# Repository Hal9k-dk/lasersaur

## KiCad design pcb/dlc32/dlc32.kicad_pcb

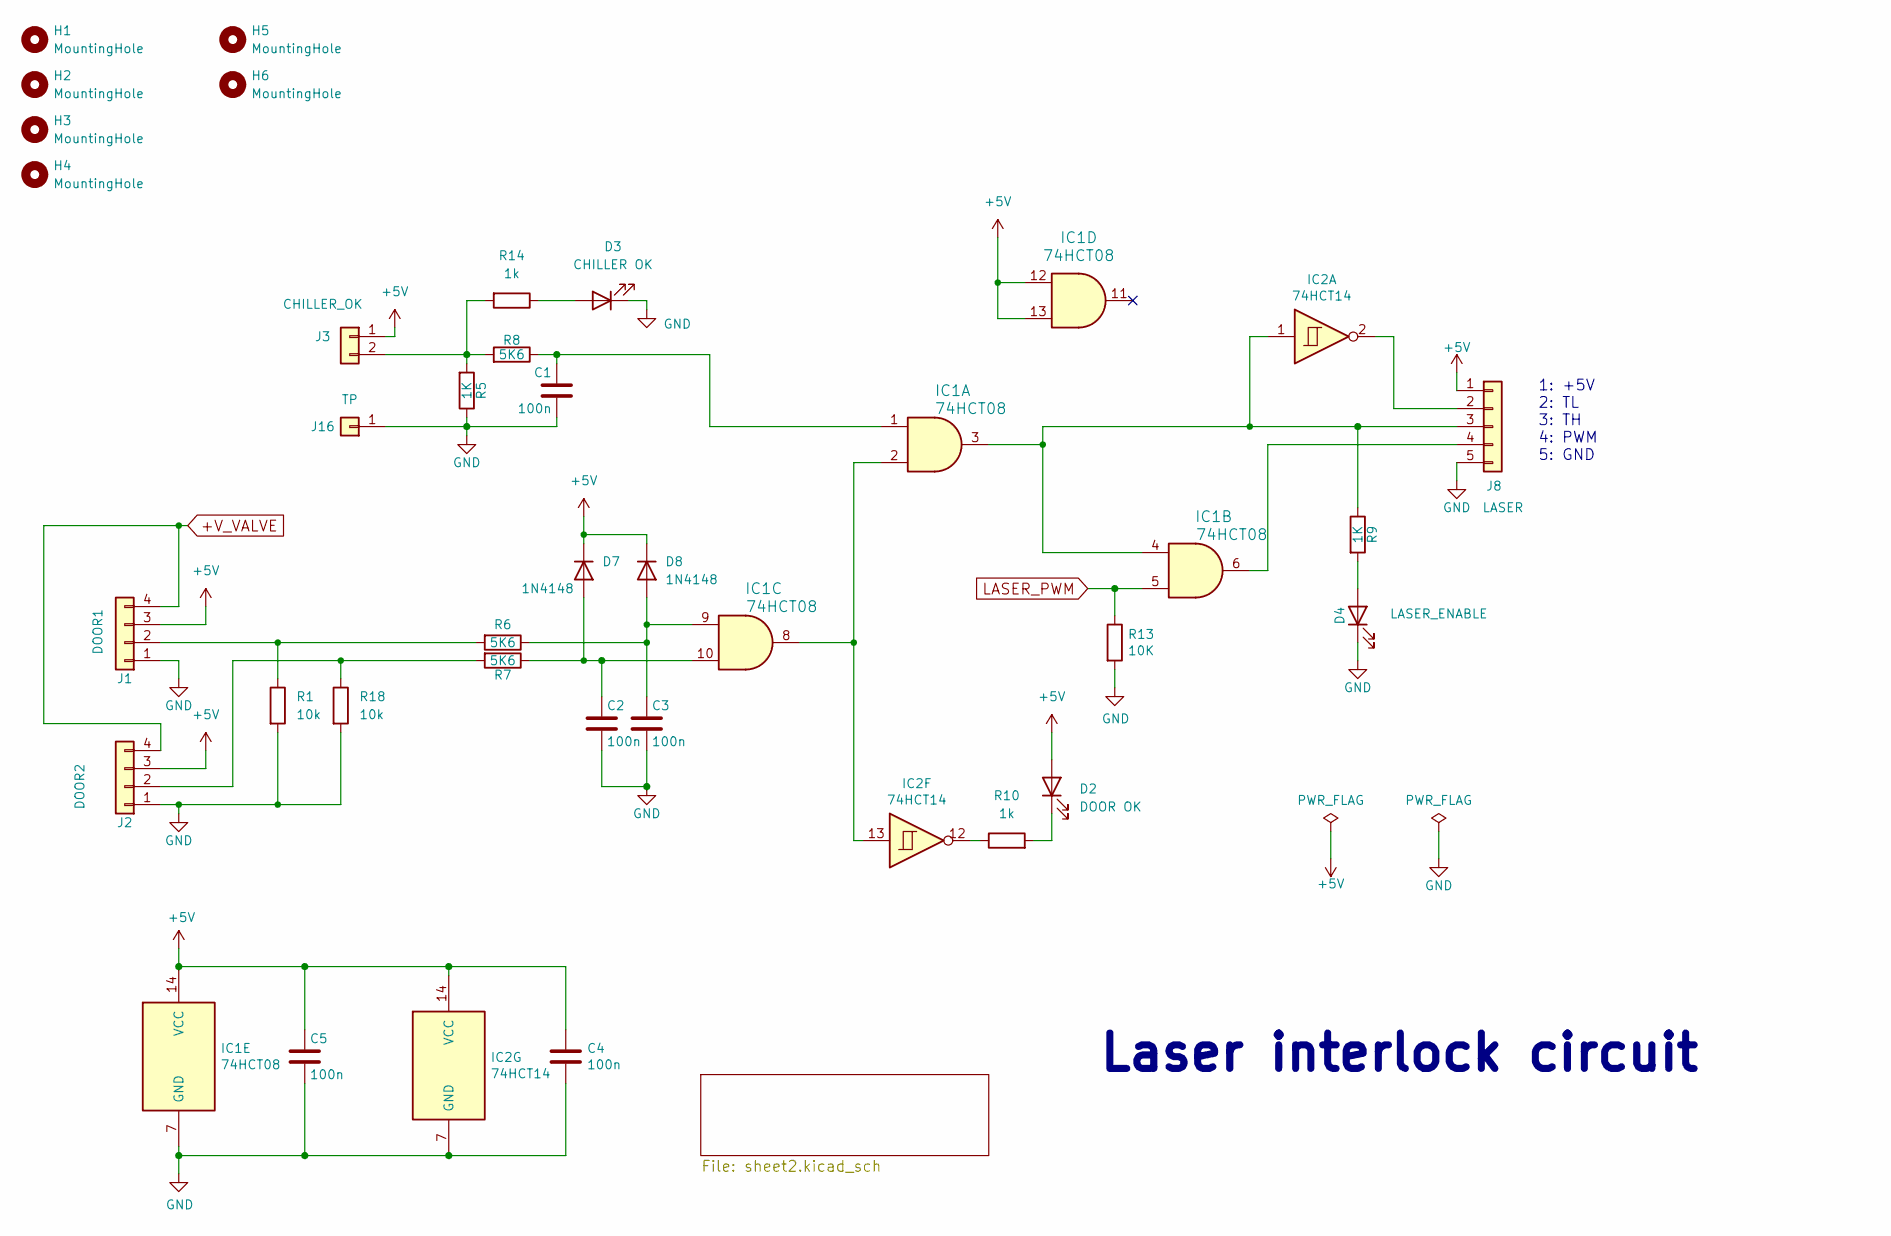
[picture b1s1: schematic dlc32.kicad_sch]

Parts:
C1, C2, C3, C4, C5: 100n; C_0603_1608Metric
D2: DOOR OK; LED_D5.0mm_Horizontal_O1.27mm_Z3.0mm
D3: CHILLER OK; LED_D5.0mm_Horizontal_O1.27mm_Z3.0mm
D4: LASER_ENABLE; LED_D5.0mm_Horizontal_O1.27mm_Z3.0mm
D7, D8: 1N4148; D_MiniMELF
H1, H2, H3, H4, H5, H6: MountingHole; MountingHole_3.2mm_M3
IC1: 74HCT08; SOIC-14_3.9x8.7mm_P1.27mm
IC2: 74HCT14; SOIC-14_3.9x8.7mm_P1.27mm
J1: DOOR1; JST_XH_B4B-XH-A_1x04_P2.50mm_Vertical
J2: DOOR2; JST_XH_B4B-XH-A_1x04_P2.50mm_Vertical
J3: CHILLER_OK; JST_XH_B2B-XH-A_1x02_P2.50mm_Vertical
J8: LASER; JST_XH_B5B-XH-A_1x05_P2.50mm_Vertical
J16: TP; TestPoint_Loop_D1.80mm_Drill1.0mm_Beaded
R1, R18: 10k; R_0603_1608Metric
R5, R9: 1K; R_0603_1608Metric
R6, R7, R8: 5K6; R_0603_1608Metric
R10, R14: 1k; R_0603_1608Metric
R13: 10K; R_0603_1608Metric

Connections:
+5V: C4.1, C5.1, D2.2 (A), D7.1 (K), D8.1 (K), IC1.12, IC1.13, IC1.14 (VCC), IC2.14 (VCC), J1.3, J2.3, J3.1, J8.1; also elsewhere on the board
+V_VALVE: J1.4, J2.4; also elsewhere on the board
GND: C1.2, C2.2, C3.2, C4.2, C5.2, D3.1 (K), D4.1 (K), IC1.7 (GND), IC2.7 (GND), J1.1, J2.1, J8.5, J16.1, R1.2, R5.1, R13.2, R18.2; also elsewhere on the board
LASER_PWM: IC1.5, R13.1; also elsewhere on the board
unnamed: C1.1, IC1.1, R8.1
unnamed: D2.1 (K), R10.2
unnamed: D3.2 (A), R14.1
unnamed: D4.2 (A), R9.2
unnamed: C2.1, D7.2 (A), IC1.10, R7.1
unnamed: C3.1, D8.2 (A), IC1.9, R6.1
unnamed: IC1.2, IC1.8, IC2.13
unnamed: IC2.12, R10.1
unnamed: J1.2, R1.1, R6.2
unnamed: J2.2, R7.2, R18.1
unnamed: J3.2, R5.2, R8.2, R14.2
unnamed: IC2.2, J8.2
unnamed: IC1.3, IC1.4, IC2.1, J8.3, R9.1
unnamed: IC1.6, J8.4

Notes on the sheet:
Laser interlock circuit
1: +5V 2: TL 3: TH 4: PWM 5: GND

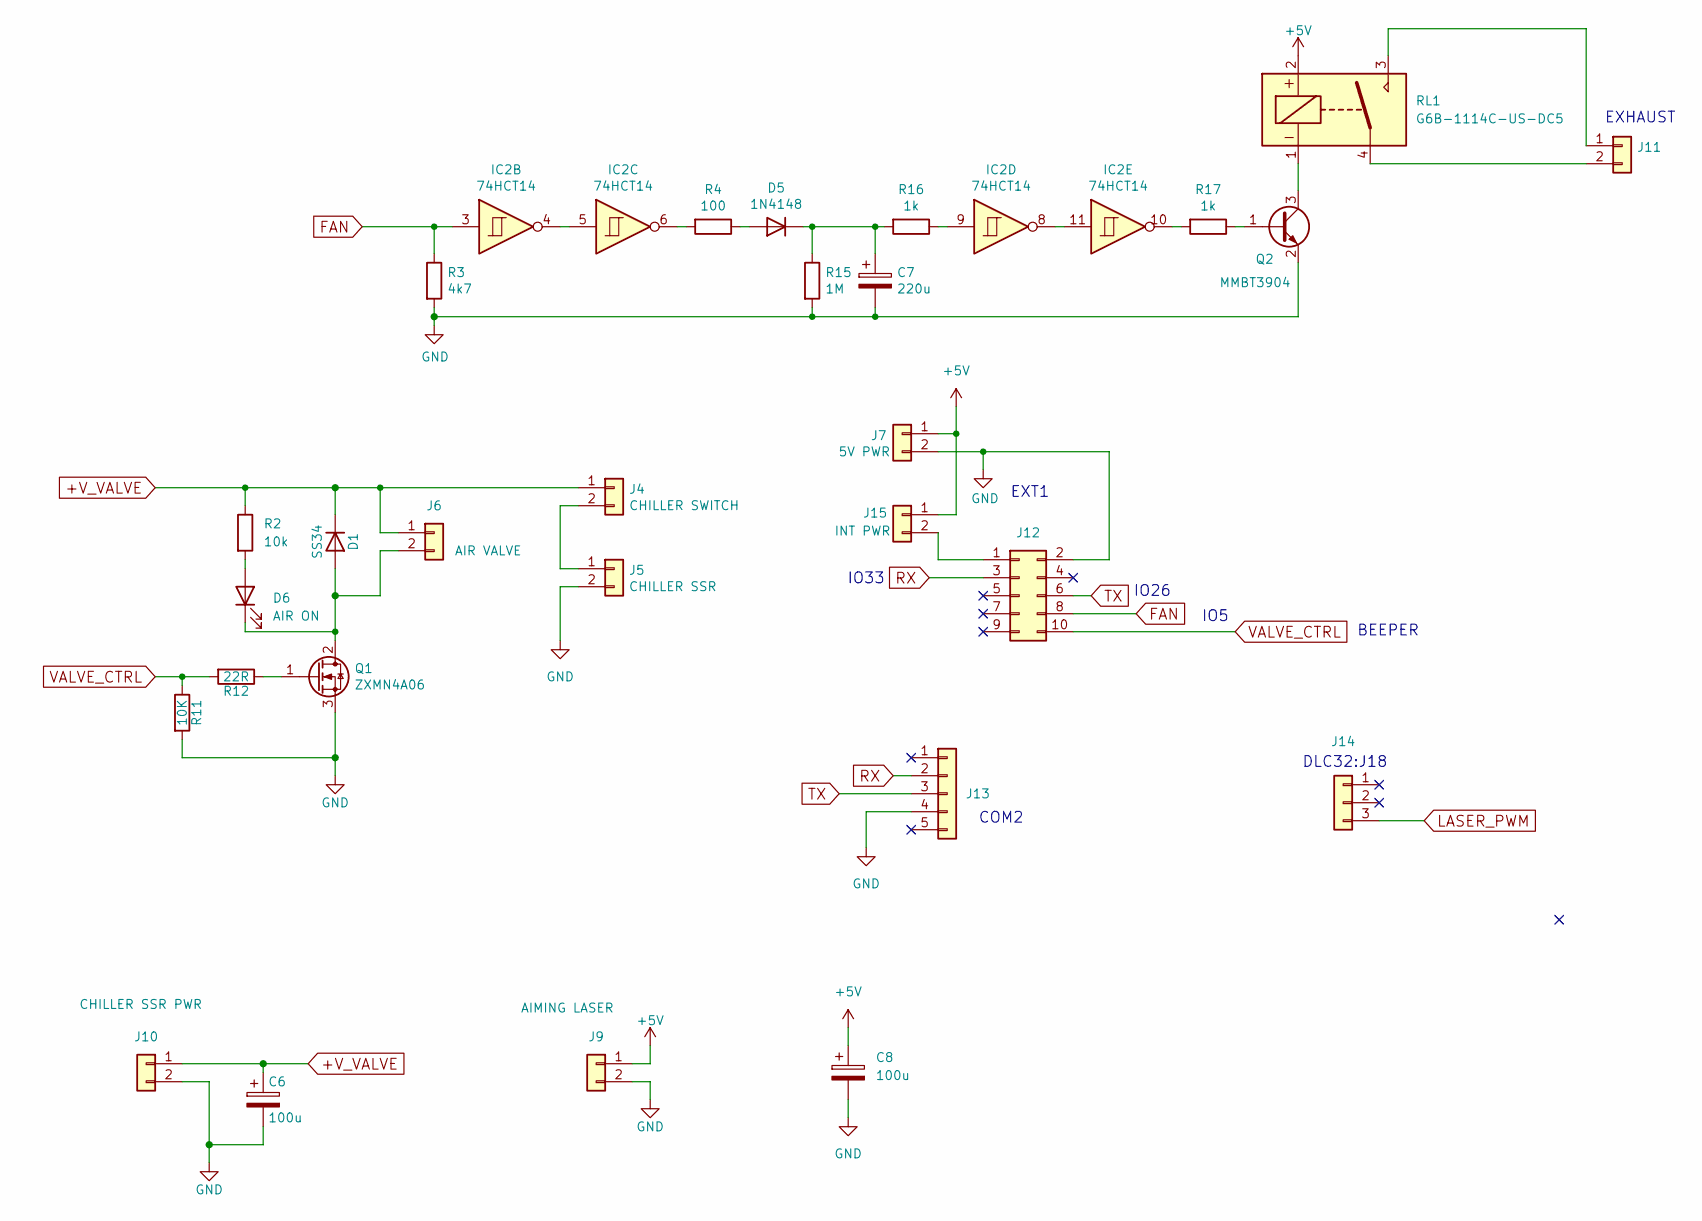
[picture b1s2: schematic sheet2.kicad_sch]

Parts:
C6, C8: 100u; CP_Elec_10x10
C7: 220u; CP_EIA-7343-15_Kemet-W
D1: SS34; D_SMA
D5: 1N4148; D_MiniMELF
D6: AIR ON; LED_D5.0mm_Horizontal_O1.27mm_Z3.0mm
IC2: 74HCT14; SOIC-14_3.9x8.7mm_P1.27mm
J4: CHILLER SWITCH; JST_XH_B2B-XH-A_1x02_P2.50mm_Vertical
J5: CHILLER SSR; JST_XH_B2B-XH-A_1x02_P2.50mm_Vertical
J6: AIR VALVE; JST_XH_B2B-XH-A_1x02_P2.50mm_Vertical
J7: 5V PWR; JST_XH_B2B-XH-A_1x02_P2.50mm_Vertical
J9: AIMING LASER; JST_XH_B2B-XH-A_1x02_P2.50mm_Vertical
J10: CHILLER SSR PWR; JST_XH_B2B-XH-A_1x02_P2.50mm_Vertical
J11: EXHAUST; JST_XH_B2B-XH-A_1x02_P2.50mm_Vertical
J12: EXT1; IDC-Header_2x05_P2.54mm_Vertical
J13: COM2; PinHeader_1x05_P2.54mm_Vertical
J14: DLC32:J18; JST_XH_B3B-XH-A_1x03_P2.50mm_Vertical
J15: INT PWR; PinHeader_1x02_P2.54mm_Vertical
Q1: ZXMN4A06; SOT-223-3_TabPin2
Q2: MMBT3904; SOT-23
R2: 10k; R_0603_1608Metric
R3: 4k7; R_0603_1608Metric
R4: 100; R_0603_1608Metric
R11: 10K; R_0603_1608Metric
R12: 22R; R_0603_1608Metric
R15: 1M; R_0603_1608Metric
R16, R17: 1k; R_0603_1608Metric
RL1: G6B-1114C-US-DC5; DIL-relay

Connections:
+5V: C8.1, J7.1, J9.1, J15.1, RL1.2; also elsewhere on the board
+V_VALVE: C6.1, D1.1 (K), J4.1, J6.1, J10.1, R2.1; also elsewhere on the board
FAN: IC2.3, J12.8, R3.1
GND: C6.2, C7.2, C8.2, J5.2, J7.2, J9.2, J10.2, J12.2, J13.4, Q1.3 (S), Q2.2 (E), R3.2, R11.2, R15.2; also elsewhere on the board
LASER_PWM: J14.3; also elsewhere on the board
unnamed: D1.2 (A), D6.1 (K), J6.2, Q1.2 (D)
unnamed: D5.2 (A), R4.1
unnamed: C7.1, D5.1 (K), R15.1, R16.2
unnamed: D6.2 (A), R2.2
unnamed: IC2.4, IC2.5
unnamed: IC2.6, R4.2
unnamed: IC2.9, R16.1
unnamed: IC2.10, R17.2
unnamed: IC2.8, IC2.11
unnamed: J4.2, J5.1
unnamed: J11.1, RL1.3
unnamed: J11.2, RL1.4
unnamed: J12.1, J15.2
unnamed: Q1.1 (G), R12.1
unnamed: Q2.1 (B), R17.1
unnamed: Q2.3 (C), RL1.1
RX: J12.3, J13.2
TX: J12.6, J13.3
VALVE_CTRL: J12.10, R11.1, R12.2

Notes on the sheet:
EXT1
EXHAUST
DLC32:J18
COM2
IO33
IO5
BEEPER
IO26

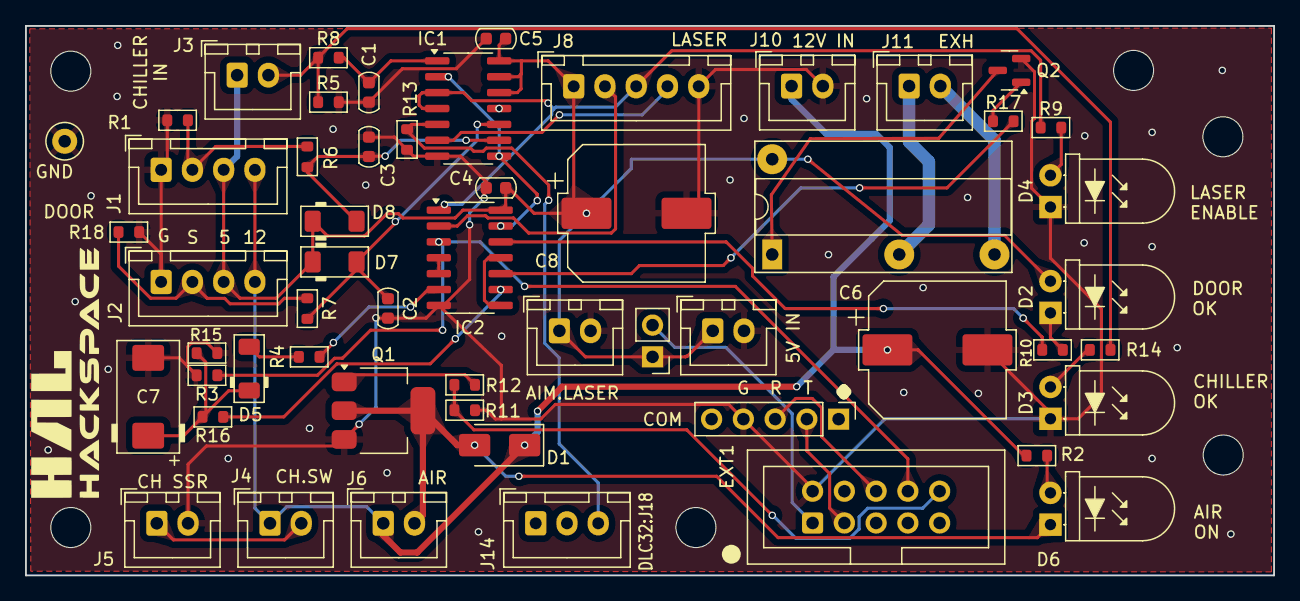
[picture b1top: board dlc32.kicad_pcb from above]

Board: 2 copper layers, 99.8 x 43.9 mm, 61 parts (0 on the bottom side), 38 nets.

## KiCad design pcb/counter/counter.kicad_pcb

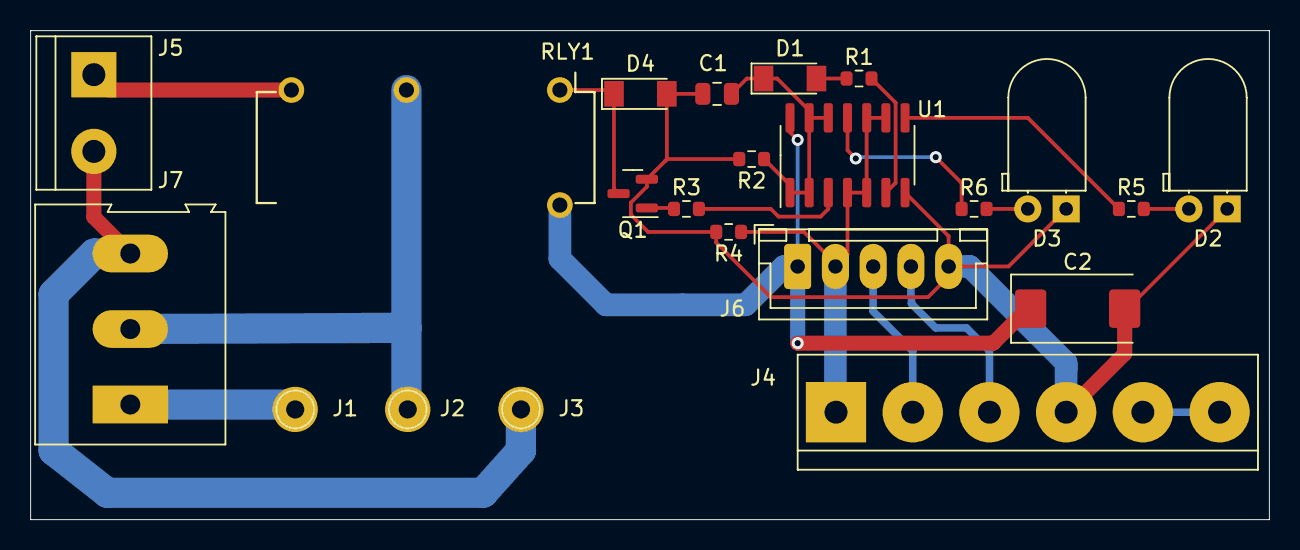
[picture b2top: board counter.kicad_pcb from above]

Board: 2 copper layers, 82.0 x 32.4 mm, 22 parts (0 on the bottom side), 20 nets.

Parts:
C1: 10u; C_0805_2012Metric
C2: 100u; CP_EIA-7343-40_Kemet-Y
D1, D4: 1N4148; D_MiniMELF
D2, D3: LED; LED_D5.0mm_Horizontal_O1.27mm_Z3.0mm
J1, J2, J3: Conn_01x01; Pin_D1.0mm_L10.0mm
J4: 0.2"; TerminalBlock_bornier-6_P5.08mm
J5: 0.2"; TerminalBlock_bornier-2_P5.08mm
J6: JST XH; JST_XH_B05B-XH-A_1x05_P2.50mm_Vertical
J7: 0.2"; TerminalBlock_Altech_AK300-3_P5.00mm
Q1: MMBT3904; SOT-23
R1: 100; R_0603_1608Metric
R2: 1M; R_0603_1608Metric
R3: 1k; R_0603_1608Metric
R4: 100k; R_0603_1608Metric
R5, R6: 820; R_0603_1608Metric
RLY1: RELAY_DIL16; DIP-16_Relay
U1: 74HCT08; SOIC-14_3.9x8.7mm_P1.27mm

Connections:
+5V: C2.1, J6.1, RLY1.16, U1.14 (VCC)
GND: C1.2, C2.2, D2.1 (K), D3.1 (K), D4.2 (A), J4.4, J6.5, Q1.2 (E), R2.2, R4.2, U1.7 (GND)
unnamed: C1.1, D1.1 (K), R2.1, U1.1, U1.2, U1.12, U1.13
unnamed: D1.2 (A), R1.1
unnamed: D2.2 (A), R5.2
unnamed: D3.2 (A), R6.2
unnamed: J1.1, J7.1
unnamed: J2.1, J7.2, RLY1.5
unnamed: J3.1, J5.2, J7.3
unnamed: J4.2, J6.3
unnamed: J4.3, J6.4
unnamed: J4.5, J4.6
unnamed: J5.1, RLY1.8
unnamed: Q1.1 (B), R3.1
unnamed: R1.2, U1.6
unnamed: R3.2, U1.3
unnamed: R5.1, U1.8
unnamed: R6.1, U1.11
RELAY: D4.1 (K), Q1.3 (C), RLY1.1
TH: J4.1, J6.2, R4.1, U1.4, U1.5, U1.9, U1.10

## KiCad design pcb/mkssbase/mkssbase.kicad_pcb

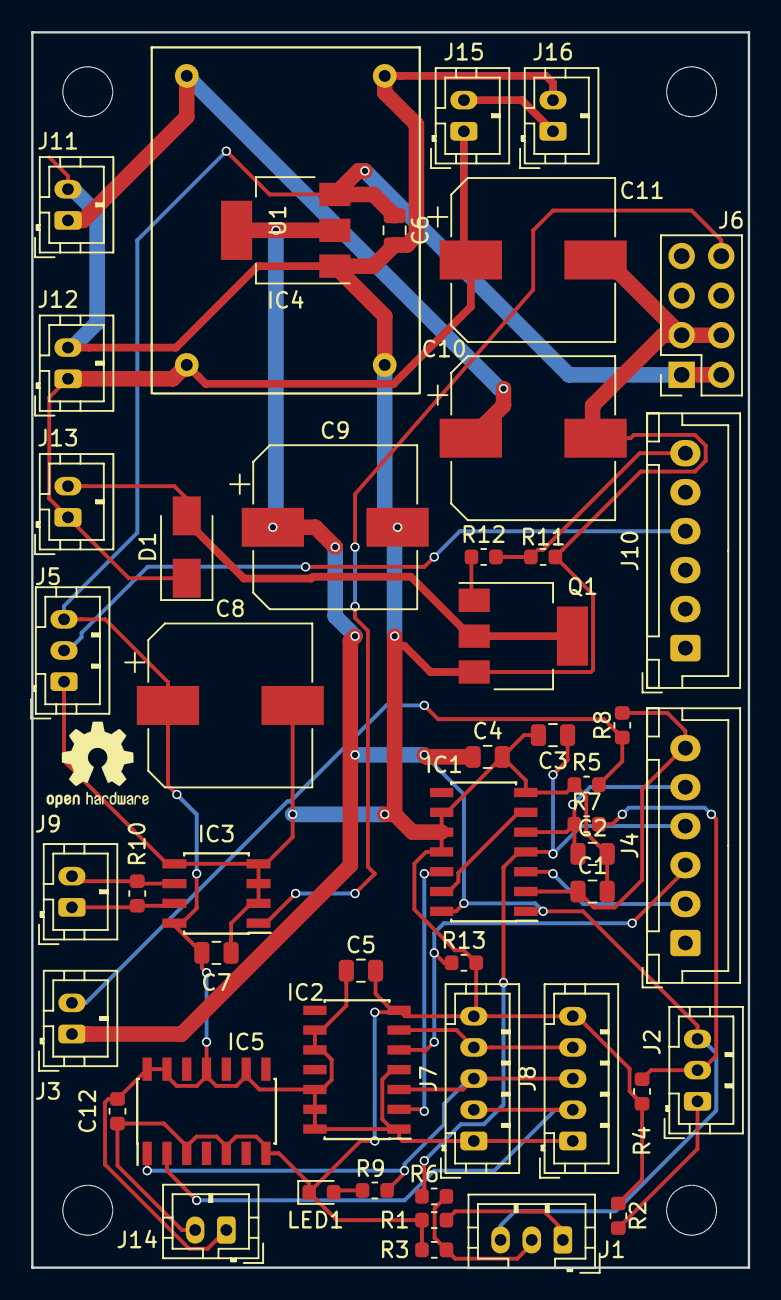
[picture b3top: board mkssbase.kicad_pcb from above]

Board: 2 copper layers, 46.0 x 79.2 mm, 50 parts (0 on the bottom side), 29 nets.

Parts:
C1, C2, C3, C4, C5, C6, C7: 100n; C_0805_2012Metric
C8, C9, C10, C11: 100u; CP_Elec_10x10
C12: 100n; C_0603_1608Metric
D1: SS34; D_SMA
IC1: 74LV11; SOIC-14_3.9x8.7mm_P1.27mm
IC2: 74HCT08; SOIC-14_3.9x8.7mm_P1.27mm
IC3: MAX485E; SOIC-8_3.9x4.9mm_P1.27mm
IC4: AMS1117-3.3; SOT-223-3_TabPin2
IC5: 74HCT04; SOIC-14_3.9x8.7mm_P1.27mm
J1: DOOR1; JST_PH_B3B-PH-K_1x03_P2.00mm_Vertical
J2: DOOR2; JST_PH_B3B-PH-K_1x03_P2.00mm_Vertical
J3: CHILLER; JST_PH_B2B-PH-K_1x02_P2.00mm_Vertical
J4: TO_J8; JST_XH_B06B-XH-A_1x06_P2.50mm_Vertical
J5: POWEROFF; JST_PH_B3B-PH-K_1x03_P2.00mm_Vertical
J6: Conn_02x04_Odd_Even; PinSocket_2x04_P2.54mm_Vertical
J7: LASER_AUX; JST_PH_B5B-PH-K_1x05_P2.00mm_Vertical
J8: LASER; JST_PH_B5B-PH-K_1x05_P2.00mm_Vertical
J9: CHILLER SERIAL; JST_PH_B2B-PH-K_1x02_P2.00mm_Vertical
J10: TO_J7; JST_XH_B06B-XH-A_1x06_P2.50mm_Vertical
J11: 24V PWR; JST_PH_B2B-PH-K_1x02_P2.00mm_Vertical
J12: LED LIGHTING; JST_PH_B2B-PH-K_1x02_P2.00mm_Vertical
J13: AIR VALVE; JST_PH_B2B-PH-K_1x02_P2.00mm_Vertical
J14: AIMING LASER; JST_PH_B2B-PH-K_1x02_P2.00mm_Vertical
J15: CHILLER POWER; JST_PH_B2B-PH-K_1x02_P2.00mm_Vertical
J16: CHILLER SSR; JST_PH_B2B-PH-K_1x02_P2.00mm_Vertical
LED1: Enable; LED_0603_1608Metric
Q1: ZXMN4A06; SOT-223-3_TabPin2
R1, R2: 100; R_0603_1608Metric
R3, R4, R5, R9: 1K; R_0603_1608Metric
R6, R7, R8: 5K6; R_0603_1608Metric
R10: 120R; R_0603_1608Metric
R11, R13: 10K; R_0603_1608Metric
R12: 22R; R_0603_1608Metric
U1: MP1584 module; MP1584-module

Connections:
+3V3: C4.1, C9.1, IC1.1, IC1.14, IC4.2, J1.3, J2.3, J3.1
+5V: C5.1, C6.1, C7.1, C8.1, C12.1, IC2.1, IC2.4, IC2.9, IC2.10, IC2.12, IC2.13, IC2.14, IC3.8, IC4.3, IC5.9, IC5.11, IC5.13, IC5.14, J5.3, J6.1, J6.2, J7.1, J8.1, J14.1
GND: C1.2, C2.2, C3.2, C4.2, C5.2, C6.2, C7.2, C8.2, C9.2, C10.2, C11.2, C12.2, IC1.7, IC1.9, IC1.10, IC1.11, IC2.7, IC3.2, IC3.3, IC3.4, IC3.5, IC4.1, IC5.3, IC5.5, IC5.7, J5.1, J6.3, J6.4, J7.5, J8.5, J11.2, J12.2, J14.2, J16.2, LED1.1, Q1.3, R1.2, R2.2, R3.2, R4.2, R5.1, R11.2, R13.2, U1.IN-, U1.OUT-
unnamed: C10.1, J11.1, U1.IN+
unnamed: C11.1, D1.1, J12.1, J13.1, J15.1, U1.OUT+
unnamed: D1.2, J13.2, Q1.2
unnamed: IC1.12, IC2.2
unnamed: IC1.6, IC1.13
unnamed: IC2.3, IC5.1, J7.3, J8.3, R9.1
unnamed: IC2.6, J7.4, J8.4
unnamed: IC3.6, J9.2, R10.2
unnamed: IC3.7, J9.1, R10.1
unnamed: IC5.2, J7.2, J8.2
unnamed: J1.1, R1.1
unnamed: J1.2, R3.1, R6.2
unnamed: J2.1, R2.1
unnamed: J2.2, R4.1, R7.2
unnamed: J3.2, R5.2, R8.2
unnamed: J5.2, J10.4
unnamed: J10.6, R11.1, R12.2
unnamed: J15.2, J16.1
unnamed: LED1.2, R9.2
unnamed: Q1.1, R12.1
P1.22: IC1.3, J4.2
P1.23: IC2.5, J4.3, R13.1
P2.11: C2.1, IC1.5, J4.5, R7.1
P2.12: C3.1, IC1.4, J4.4, R6.1
P4.28: C1.1, IC1.2, J4.6, R8.1
RX: IC3.1, J6.8

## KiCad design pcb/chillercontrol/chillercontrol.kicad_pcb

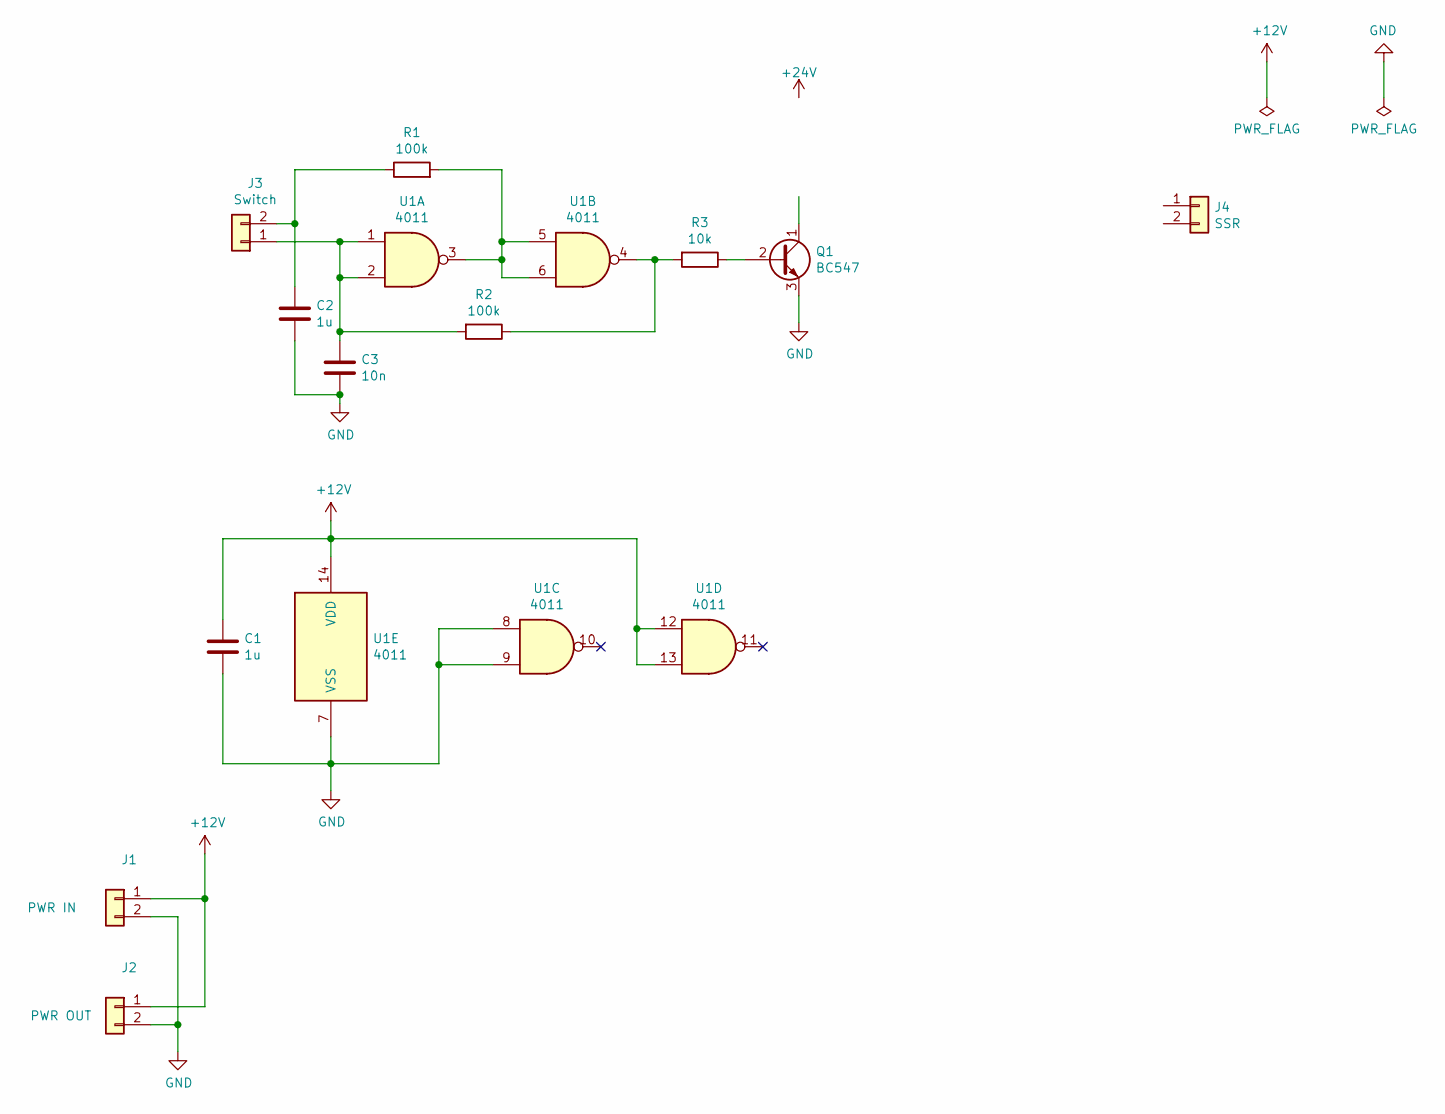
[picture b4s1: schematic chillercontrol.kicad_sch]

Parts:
C1, C2: 1u; C_Rect_L7.0mm_W6.0mm_P5.00mm
C3: 10n; C_Disc_D8.0mm_W2.5mm_P5.00mm
J1: PWR IN; JST_PH_B2B-PH-K_1x02_P2.00mm_Vertical
J2: PWR OUT; JST_PH_B2B-PH-K_1x02_P2.00mm_Vertical
J3: Switch; JST_PH_B2B-PH-K_1x02_P2.00mm_Vertical
J4: SSR; JST_PH_B2B-PH-K_1x02_P2.00mm_Vertical
Q1: BC547; TO-92L_Wide
R1, R2: 100k; R_Axial_DIN0207_L6.3mm_D2.5mm_P5.08mm_Vertical
R3: 10k; R_Axial_DIN0207_L6.3mm_D2.5mm_P5.08mm_Vertical
U1: 4011; DIP-14_W7.62mm_LongPads

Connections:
+12V: C1.1, J1.1, J2.1, J4.1, U1.12, U1.13, U1.14 (VDD)
GND: C1.2, C2.2, C3.2, J1.2, J2.2, Q1.3 (E), U1.7 (VSS), U1.8, U1.9
unnamed: C2.1, J3.2, R1.1
unnamed: C3.1, J3.1, R2.2, U1.1, U1.2
unnamed: J4.2, Q1.1 (C)
unnamed: Q1.2 (B), R3.1
unnamed: R1.2, U1.3, U1.5, U1.6
unnamed: R2.1, R3.2, U1.4

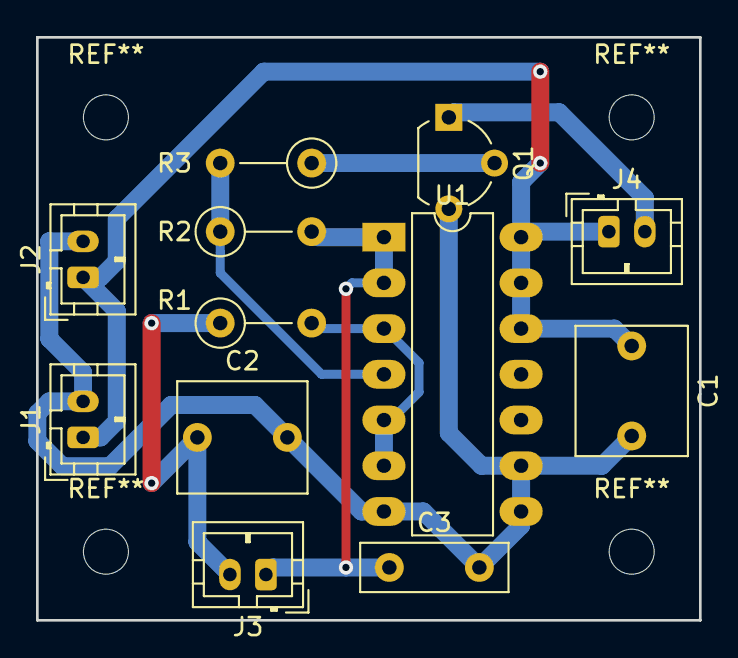
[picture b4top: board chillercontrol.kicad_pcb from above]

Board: 2 copper layers, 36.8 x 32.4 mm, 12 parts (0 on the bottom side), 8 nets.

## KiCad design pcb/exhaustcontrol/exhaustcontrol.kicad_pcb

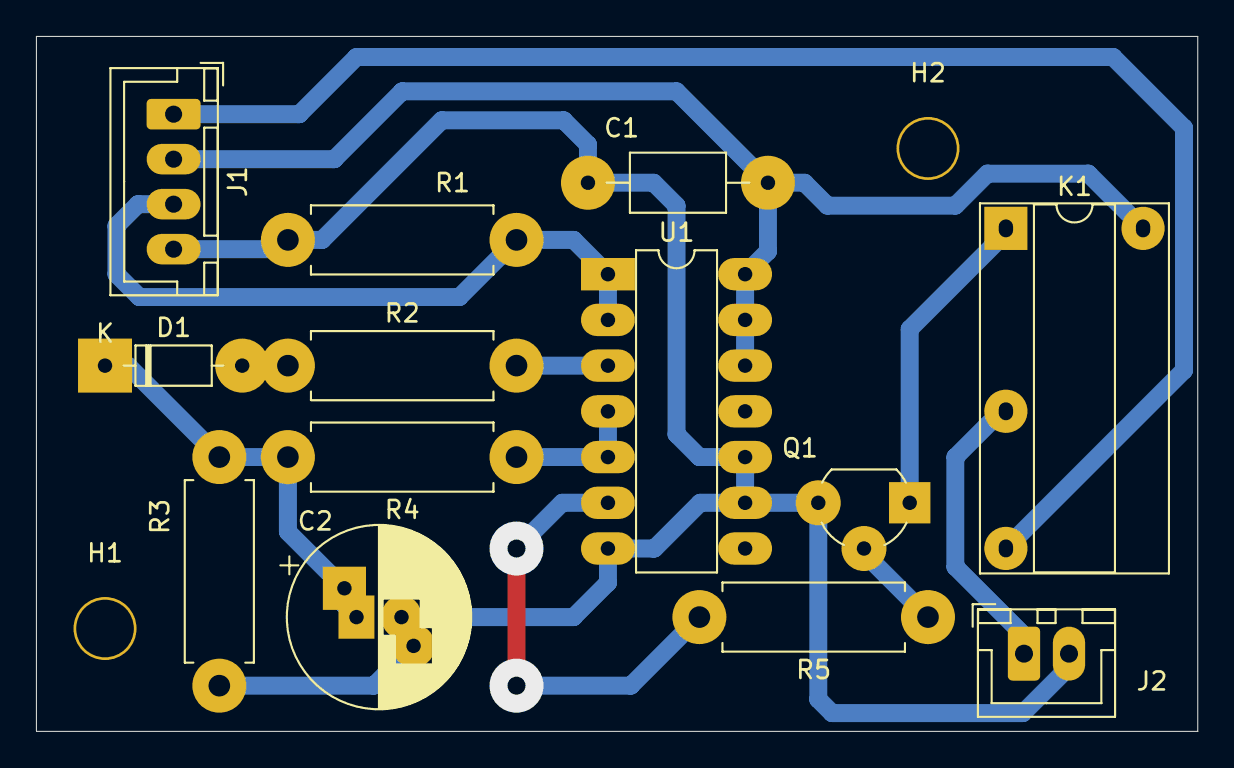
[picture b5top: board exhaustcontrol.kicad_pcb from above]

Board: 2 copper layers, 64.5 x 38.6 mm, 15 parts (0 on the bottom side), 12 nets.

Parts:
C1: 100n; C_Axial_L5.1mm_D3.1mm_P10.00mm_Horizontal
C2: 220u; CP_Radial_D10.0mm_P2.50mm_P5.00mm
D1: 1N4148; D_DO-35_SOD27_P7.62mm_Horizontal
H1, H2: MountingHole; MountingHole_3.2mm_M3
J1: JST XH; JST_XH_B04B-XH-A_1x04_P2.50mm_Vertical
J2: Conn_01x02; JST_XH_B02B-XH-A_1x02_P2.50mm_Vertical
K1: UMS05-1A80-75D; DIL-relay
Q1: BC547; TO-92_Wide
R1: 4k7; R_Axial_DIN0411_L9.9mm_D3.6mm_P12.70mm_Horizontal
R2: 100; R_Axial_DIN0411_L9.9mm_D3.6mm_P12.70mm_Horizontal
R3: 1M; R_Axial_DIN0411_L9.9mm_D3.6mm_P12.70mm_Horizontal
R4, R5: 1k; R_Axial_DIN0411_L9.9mm_D3.6mm_P12.70mm_Horizontal
U1: 74HC08; DIP-14_W7.62mm_LongPads

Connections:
+5V: C1.1, J1.2, K1.2, U1.12, U1.13, U1.14 (VCC)
+24V: J1.1, K1.4
GND: C1.2, C2.2, J1.4, J2.2, Q1.3 (E), R1.2, R3.2, U1.7 (GND), U1.9, U1.10
unnamed: C2.1, D1.1 (K), R3.1, R4.2
unnamed: D1.2 (A), R2.1
unnamed: J1.3, R1.1, U1.1, U1.2
unnamed: J2.1, K1.3
unnamed: K1.1, Q1.1 (C)
unnamed: Q1.2 (B), R5.1
unnamed: R2.2, U1.3
unnamed: R4.1, U1.4, U1.5
unnamed: R5.2, U1.6

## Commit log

2022-01-01 Copy from old repo.
2022-01-02 Fix 3D models.
2022-01-10 Update.
2022-02-24 Add links.
2022-03-06 Add more.
2022-03-06 Add TBD.
2022-03-10 Add pictures.
2022-07-15 Mount for Y-axis bearing.
2022-07-15 Mounting holes.
2022-07-22 Make card pocket a little thicker.
2022-07-23 Add holes for inserts.
2022-07-24 Tweak.
2022-10-09 Add plate for aiming laser.
2022-10-15 First shot.
2022-10-15 Add stuff.
2022-10-16 Fix hole position for ammeter.
2022-10-18 Final version.
2022-10-29 Add SVG for dashboard cutout.
2022-11-06 Update footprints for SMD version.
2022-11-07 Add protection diode; work on routing.
2022-11-10 Finish routing.
2022-11-10 Fill zones.
2022-11-10 Order.
2022-11-12 Basic structure.
2022-11-12 First version.
2022-11-18 Mirror.
2022-11-18 Add second hole.
2022-11-18 Adjust beamhole position.
2022-12-05 First attempt.
2022-12-10 Holder for standalone LED.
2022-12-29 Add screw holes.
2022-12-29 Fix bug.
2023-01-15 Adjust ID.
2023-01-28 Make room for 4 rings.
2024-09-29 Enlarge.
2025-02-07 Add as copy of mksbase.
2025-02-07 Update symbols etc, remove obsolete parts.
2025-02-07 Renumber, delete PCB.
2025-02-09 Add block diagram.
2025-02-09 Update, rename.
2025-02-09 Add DLC-32 block diagram.
2025-02-09 Include exhaust control in dlc32 pcb.
2025-02-09 Simplify.
2025-02-09 Add mounting holes.
2025-02-10 Finalize diagram.
2025-02-11 Start PCB.
2025-02-11 Use resistor array.
2025-02-12 Add optional +5V power, route.
2025-02-13 Fix footprint for R1.
2025-02-13 Update version.
2025-02-14 Add lasertester sketch.
2025-02-15 Fix pin assigments.
2025-02-15 Route some more.
2025-02-16 Route.
2025-02-16 Complete routing.
2025-02-16 Make pretty.
2025-02-27 Mount plate for MKS-DLC32 + interface board.
2025-03-01 Rewrite in build123d.
2025-03-01 Add cutout for resistor.
2025-03-01 Move resistor cutout to correct side.
2025-03-14 Use Schmitt triggers. Add clamping diodes, test point.
2025-03-15 Change to tantalum cap. Optimize connector placement.
2025-03-15 Update for smaller fiber.
2025-04-06 Save grblHAL settings, reorganize datasheets.
2025-04-06 Eliminate LASER_EN.
2025-04-07 Add original DLC32 firmware.
2025-04-07 Add grblHAL UART firmware.
2025-04-07 Fix filename.
2025-04-07 Use correct pin on DLC32:J18.
2025-04-07 Fix swapped silk screen.
2025-04-13 Save grbl-LPC settings for MKS-SBASE.
2025-04-15 Add wiring diagram.
2025-04-17 Add bracket for door sensor.
2025-04-27 Adjust.
2025-04-27 Add legend.
2025-05-04 New version (DLC32).
2025-05-08 Swap RX and TX.
2025-05-09 Update bracket.
2025-05-15 More holes.
2025-05-16 Make ridges less protruding.
2025-05-30 Update laser connector, prevent fan activation on startup.
2025-06-12 Add endstop connectors.
2025-06-19 Update settings.
2025-09-13 Retainers for Y belt
2025-09-13 Add support for dual endstops.
2025-09-27 Fix wrong pin: IO39 is actually IO19.
2025-10-02 Add mount for solenoid valve.
2025-10-02 Add slot for cable tie.
2025-10-12 Spacer for idler holder.
